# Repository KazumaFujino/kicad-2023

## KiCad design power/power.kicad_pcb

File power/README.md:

# ハードウェア
<br>
- 回路図  
<br>

## 特徴
安いコスト(秋月だけで揃う)．制御系，駆動系の絶縁．高速な駆動電源のスイッチング．

# 端子
### J1 J2
電源入力 絶縁DCDCの関係で`9～36V`の範囲．

### J3 J4
駆動電源出力

### J5
物理緊急停止

### J6 J7
メインバス．絶縁12VとCANパススルー

### J8
遠隔緊急停止  
GPIOと接続して物理緊急停止と直列に駆動電源のスイッチング．

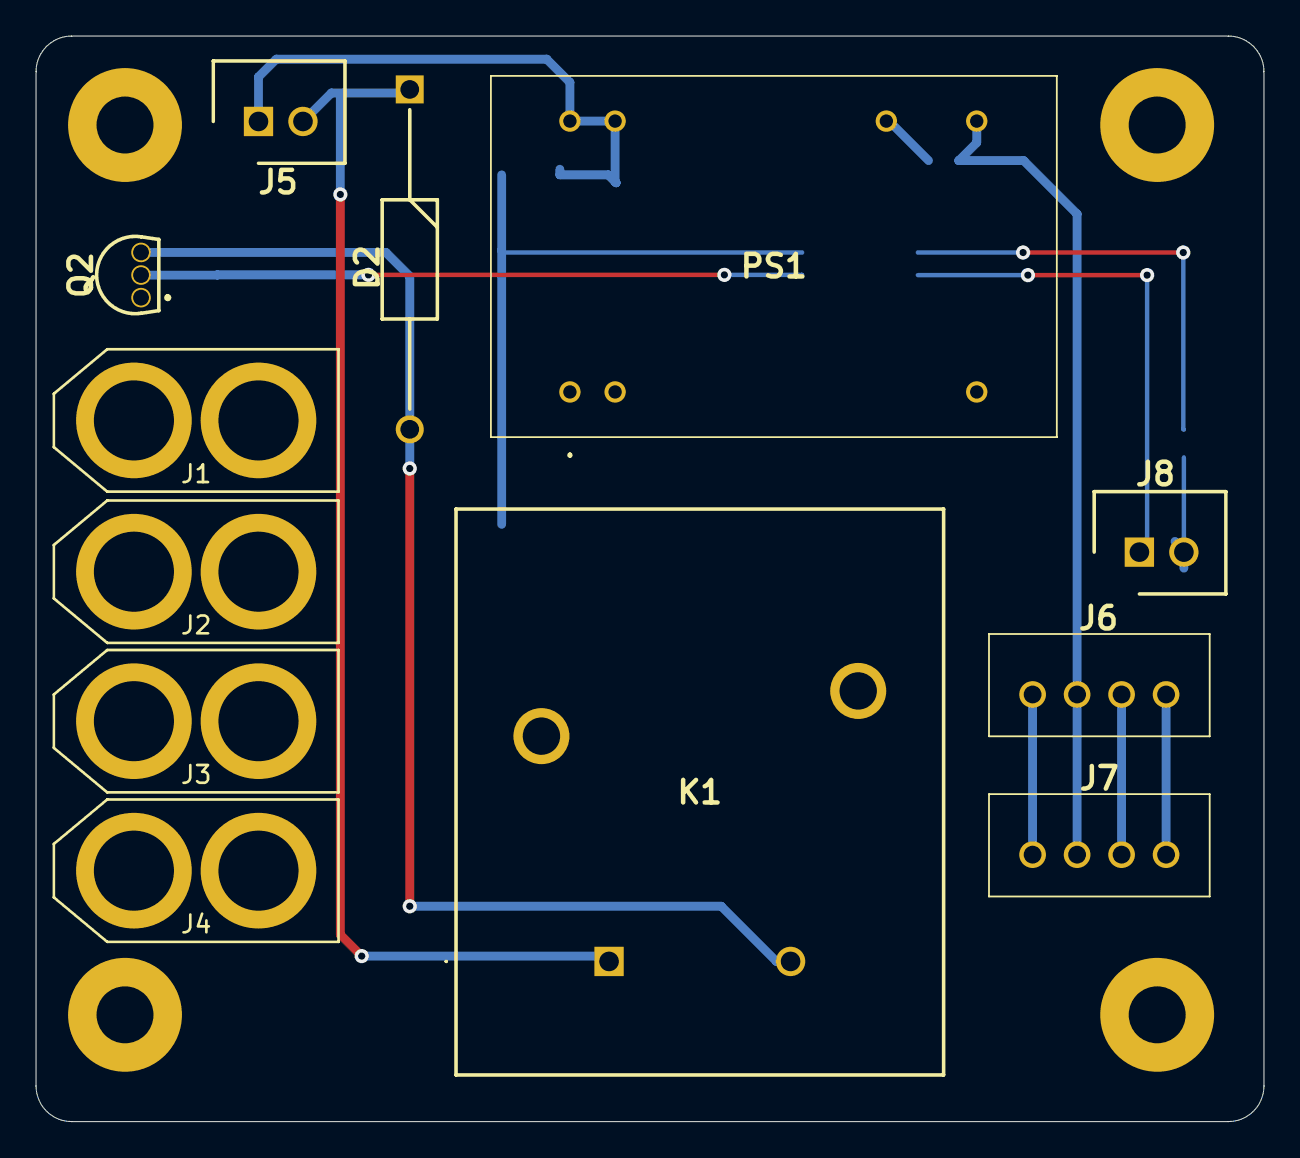
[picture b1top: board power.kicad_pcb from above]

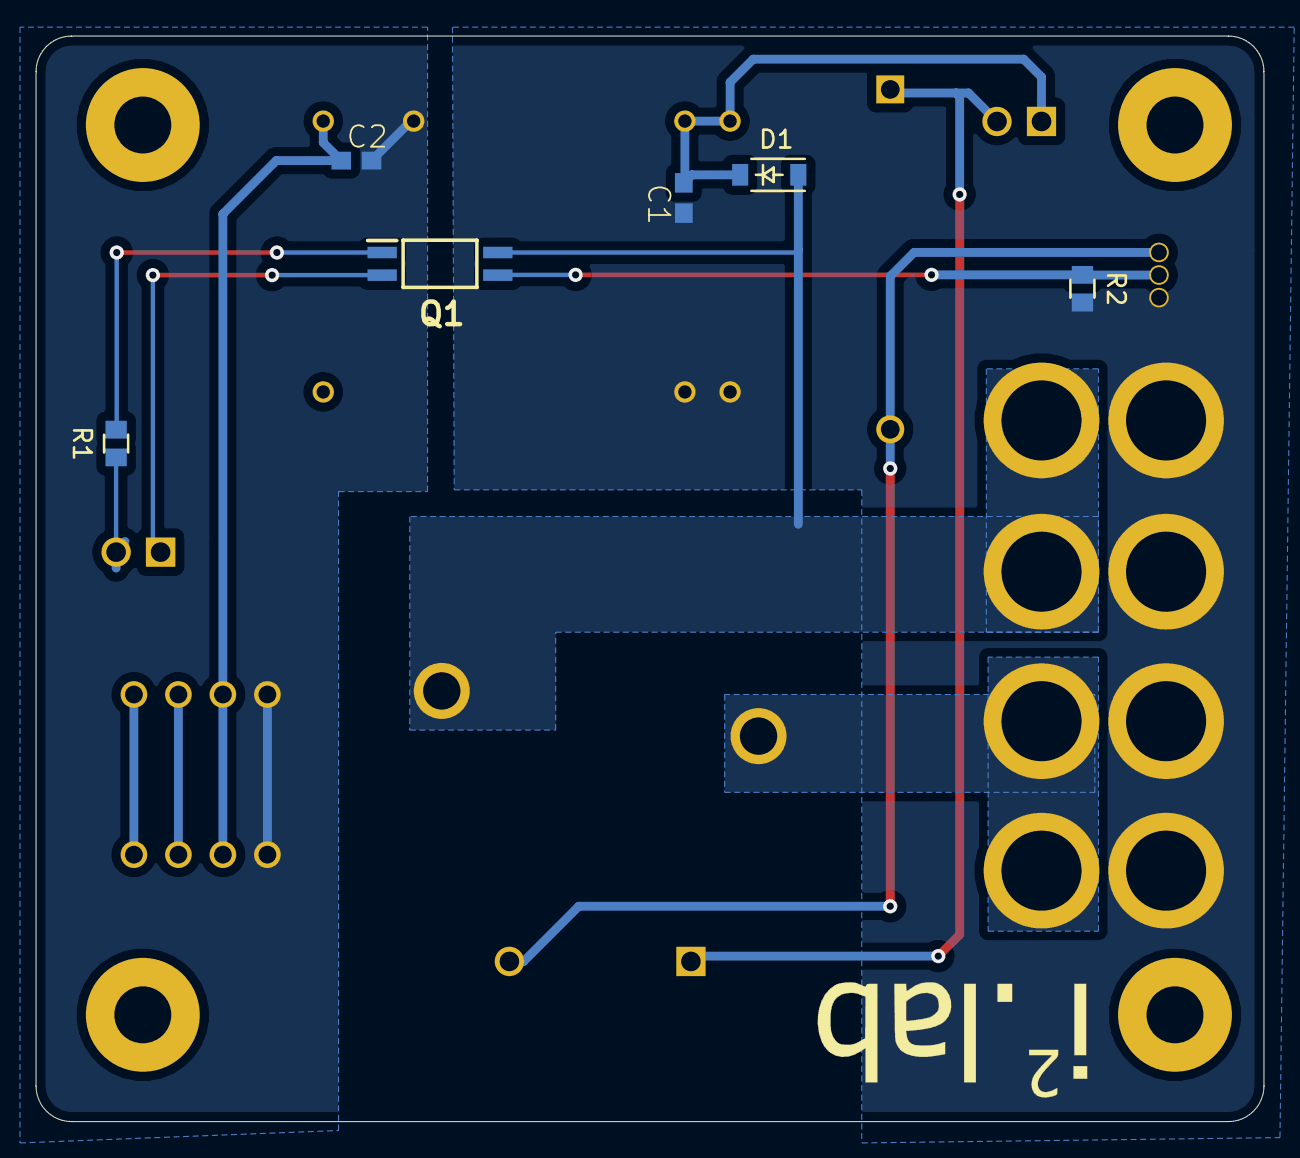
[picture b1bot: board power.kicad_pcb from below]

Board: 2 copper layers, 69.0 x 61.0 mm, 18 parts (6 on the bottom side), 14 nets.

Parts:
C1, C2: CAP; C1608
D1: DIODE; SOD-123
D2: DIOAD1910W86L670D310; SB340LS
J1, J2: Conn_01x02; XT60_M
J3, J4: Conn_01x02; XT60_F
J5, J8: SHDR2W64P0X250_1X2_740X575X700P; B2B-XH-A_LF__SN_
J6, J7: B4B-XH-A_LF__SN_; B4B-XH-A_LF__SN
K1: 9531A12DG1; 953-1A-12DG-1
PS1: MIWI0624S12; MIWI06-24S12
Q1: TLP293_V4-GBTL,E_T; TLP293_V4-GBTL_E_T
Q2: TS1107A1AP; 2N7000
R1: R1; R_1608
R2: R2; R_1608

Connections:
+12V: D1.1, J1.2, J2.2, K1.4, Q1.4
CAH_L: J6.4, J7.4
CAN_H: J6.3, J7.3
GND: C1.2, J1.1, J2.1, J3.1, J4.1, PS1.2, PS1.3, Q2.1, R2.2
GNDREF: C2.2, J6.1, J7.1, PS1.16
MOTOR_OUT: J3.2, J4.2, K1.3
unnamed: C1.1, D1.2, J5.1, PS1.22, PS1.23
unnamed: D2.1, J5.2, K1.1
unnamed: D2.2, K1.2, Q2.3
unnamed: Q1.1, R1.2
PC_GND: J8.1, Q1.2
PC_GPIO: J8.2, R1.1
PHOTO: Q1.3, Q2.2, R2.1
VCC: C2.1, J6.2, J7.2, PS1.14

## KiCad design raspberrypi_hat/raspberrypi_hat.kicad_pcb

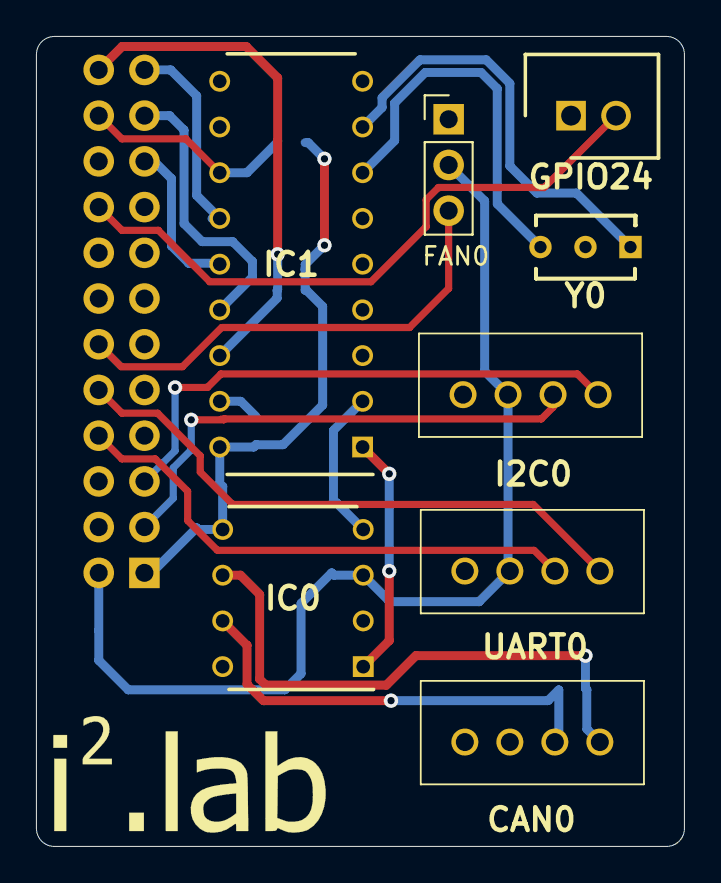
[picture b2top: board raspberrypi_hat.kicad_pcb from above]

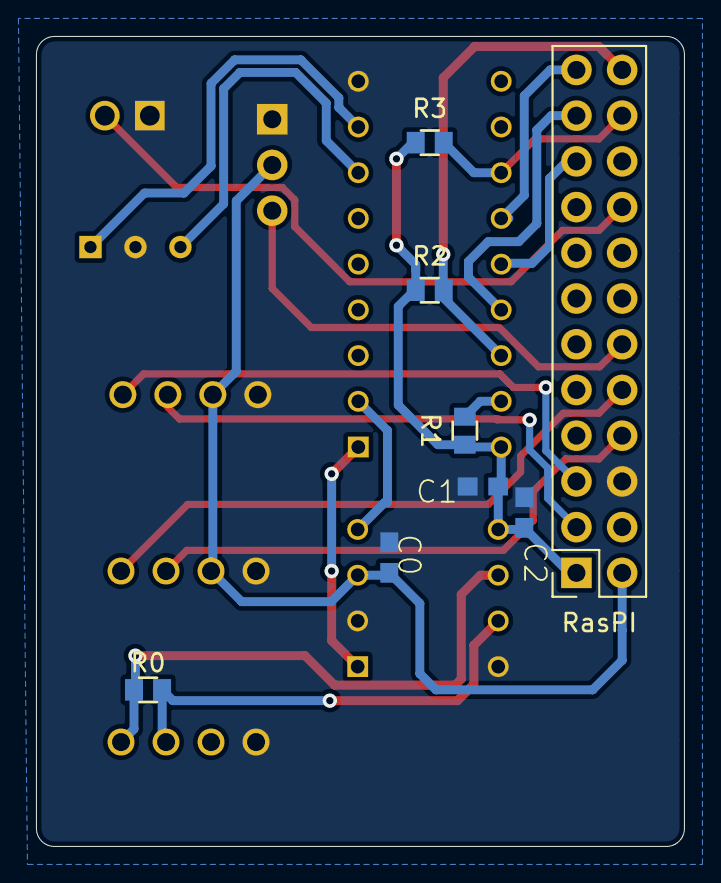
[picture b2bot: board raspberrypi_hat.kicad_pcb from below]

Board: 2 copper layers, 36.0 x 45.0 mm, 16 parts (8 on the bottom side), 21 nets.

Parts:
C0, C1, C2: CAP; C1608
CAN0: Conn_01x04; B4B-XH-A_LF__SN
FAN0: Conn_01x03; PinHeader_1x03_P2.54mm_Vertical
GPIO24: Conn_01x02; B2B-XH-A_LF__SN_
I2C0: Conn_01x04; B4B-XH-A_LF__SN
IC0: MCP2562FD-E_P
IC1: MCP2515-I_P
R0: R0; R_1608
R1: R1; R_1608
R2: R2; R_1608
R3: R3; R_1608
RasPI: Conn_02x12_Odd_Even; PinSocket_2x12_P2.54mm_Vertical
UART0: Conn_01x04; B4B-XH-A_LF__SN
Y0: CSTLS20M0X51-B0; CSTLS20M0X51B0

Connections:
+3V3: C1.1, C2.1, IC0.5, IC1.18, R1.1, R2.1, R3.1, RasPI.1
+5V: C0.1, FAN0.2, I2C0.2, IC0.3, RasPI.2, UART0.2
CAN_H: CAN0.3, IC0.7, R0.1
CAN_L: CAN0.4, IC0.6, R0.2
CE0: IC1.16, R2.2, RasPI.24
CLK: IC1.13, RasPI.23
GND: C0.2, C1.2, C2.2, CAN0.1, FAN0.1, GPIO24.1, I2C0.1, IC0.2, IC0.8, IC1.9, RasPI.6, UART0.1, Y0.2
GPIO18: FAN0.3, RasPI.12
GPIO24: GPIO24.2, RasPI.18
GPIO25: IC1.12, R3.2, RasPI.22
MISO: IC1.15, RasPI.21
MOSI: IC1.14, RasPI.19
unnamed: IC0.1, IC1.1
unnamed: IC0.4, IC1.2
unnamed: IC1.7, Y0.3
unnamed: IC1.8, Y0.1
unnamed: IC1.17, R1.2
RX: RasPI.10, UART0.4
SDA: I2C0.3, RasPI.3
SDL: I2C0.4, RasPI.5
TX: RasPI.8, UART0.3

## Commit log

2023-09-25 ✨feat:first ci
2023-09-29 📚docs:ラズパイハットのREADME
2023-10-02 📚docs:電源基板
